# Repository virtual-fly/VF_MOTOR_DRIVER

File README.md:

# VF_Motor_Driver

**VF_Motor_Driver** is an open hardware power distribution board, designed to be part of a larger modular system.  
This design is **based in part** on the [OpenFFBoard TMC4671 driver board](https://github.com/Ultrawipf/OpenFFBoard-hardware), licensed under the GNU General Public License version 3 (GPLv3).

This repository contains the complete schematic and PCB layout for the VF_Motor_Driver board.

---

## 🧩 Project Contents

- KiCad schematic files (`.kicad_sch`)
- KiCad PCB layout files (`.kicad_pcb`)
- `Library/` – Custom library symbols (if any)
- `LICENSE` – Full text of the GNU GPLv3 license
- `README.md` – Project information and license notice

---

## 🔍 Licensing

The hardware design files for **VF_Motor_Driver** are released under the terms of the **GNU General Public License, version 3 (GPLv3)**.

You are free to:
- Use and manufacture this hardware for any purpose
- Study, modify and redistribute the design
- Include this design in your own open projects

**Conditions**:
- You must publish any modified versions under the same GPLv3 license
- You must attribute the original author(s)
- You must make the complete design files available to your users if you distribute products based on this design

Author: Enric Garcia Diaz

Copyright (c) 2025 VirtualFly S.L.

See the `LICENSE` file for full details.

---

## ⚠️ Integration Notice

The VF_Motor_Driver is used as a subsystem in a commercial product developed by VirtualFly S.L.

> The VF_Motor_Driver hardware is GPLv3-licensed,  
> but the **microcontroller board and its firmware** are **not included** in this repository and are **not derived** from any GPLv3-licensed work.

---

## 📘 Attribution Notice

The microcontroller board and its firmware used in the final product are derived from the open-source project [OpenFFBoard](https://github.com/Ultrawipf/OpenFFBoard), originally developed by Yannick Richter and released under the MIT License.

The original license terms and copyright notice are preserved.

This firmware and MCU board are not included in this repository and are not covered by the GPLv3 license.

---

## 🔌 Compatibility

The VF_Motor_Driver is designed to interface with a microcontroller unit (MCU) that is electrically and functionally compatible with the [OpenFFBoard](https://github.com/Ultrawipf/OpenFFBoard) open-source project.

> The OpenFFBoard firmware and hardware are **not included** in this repository  
> and are released under the [MIT License](https://opensource.org/licenses/MIT).

Compatible with OpenFFBoard, but **designed, tested, and supported by VirtualFly** for professional use cases.

This compatibility is provided as a convenience for developers and users who already rely on the OpenFFBoard ecosystem or wish to integrate the VF_Motor_Driver into similar setups.

---

## 🤝 Contribution to the Open Source Community

The VF_Motor_Driver project is part of VirtualFly’s commitment to supporting open hardware and fostering collaboration with the developer community.

By releasing this board under the GNU GPLv3 license, we aim to:

- ✅ Provide a solid and reusable foundation for motor control and power distribution in open systems
- ✅ Extend compatibility with the existing [OpenFFBoard](https://github.com/Ultrawipf/OpenFFBoard) ecosystem
- ✅ Offer a real-world example of how open-source hardware can coexist with commercial products
- ✅ Help engineers, makers, and researchers save time and improve reliability in their own designs

We believe that innovation grows stronger when shared.  
We encourage developers to build upon this work, suggest improvements, and share their own adaptations.

If you use this project, improve it, or integrate it into a new design, feel free to [get in touch](mailto:support@virtual-fly.com) or contribute via pull requests.

Together, we can strengthen the open hardware movement.

---

## 📞 Contact

**VirtualFly S.L.**  
Website: [https://virtual-fly.com](https://virtual-fly.com)  
Email: [support@virtual-fly.com](mailto:support@virtual-fly.com)

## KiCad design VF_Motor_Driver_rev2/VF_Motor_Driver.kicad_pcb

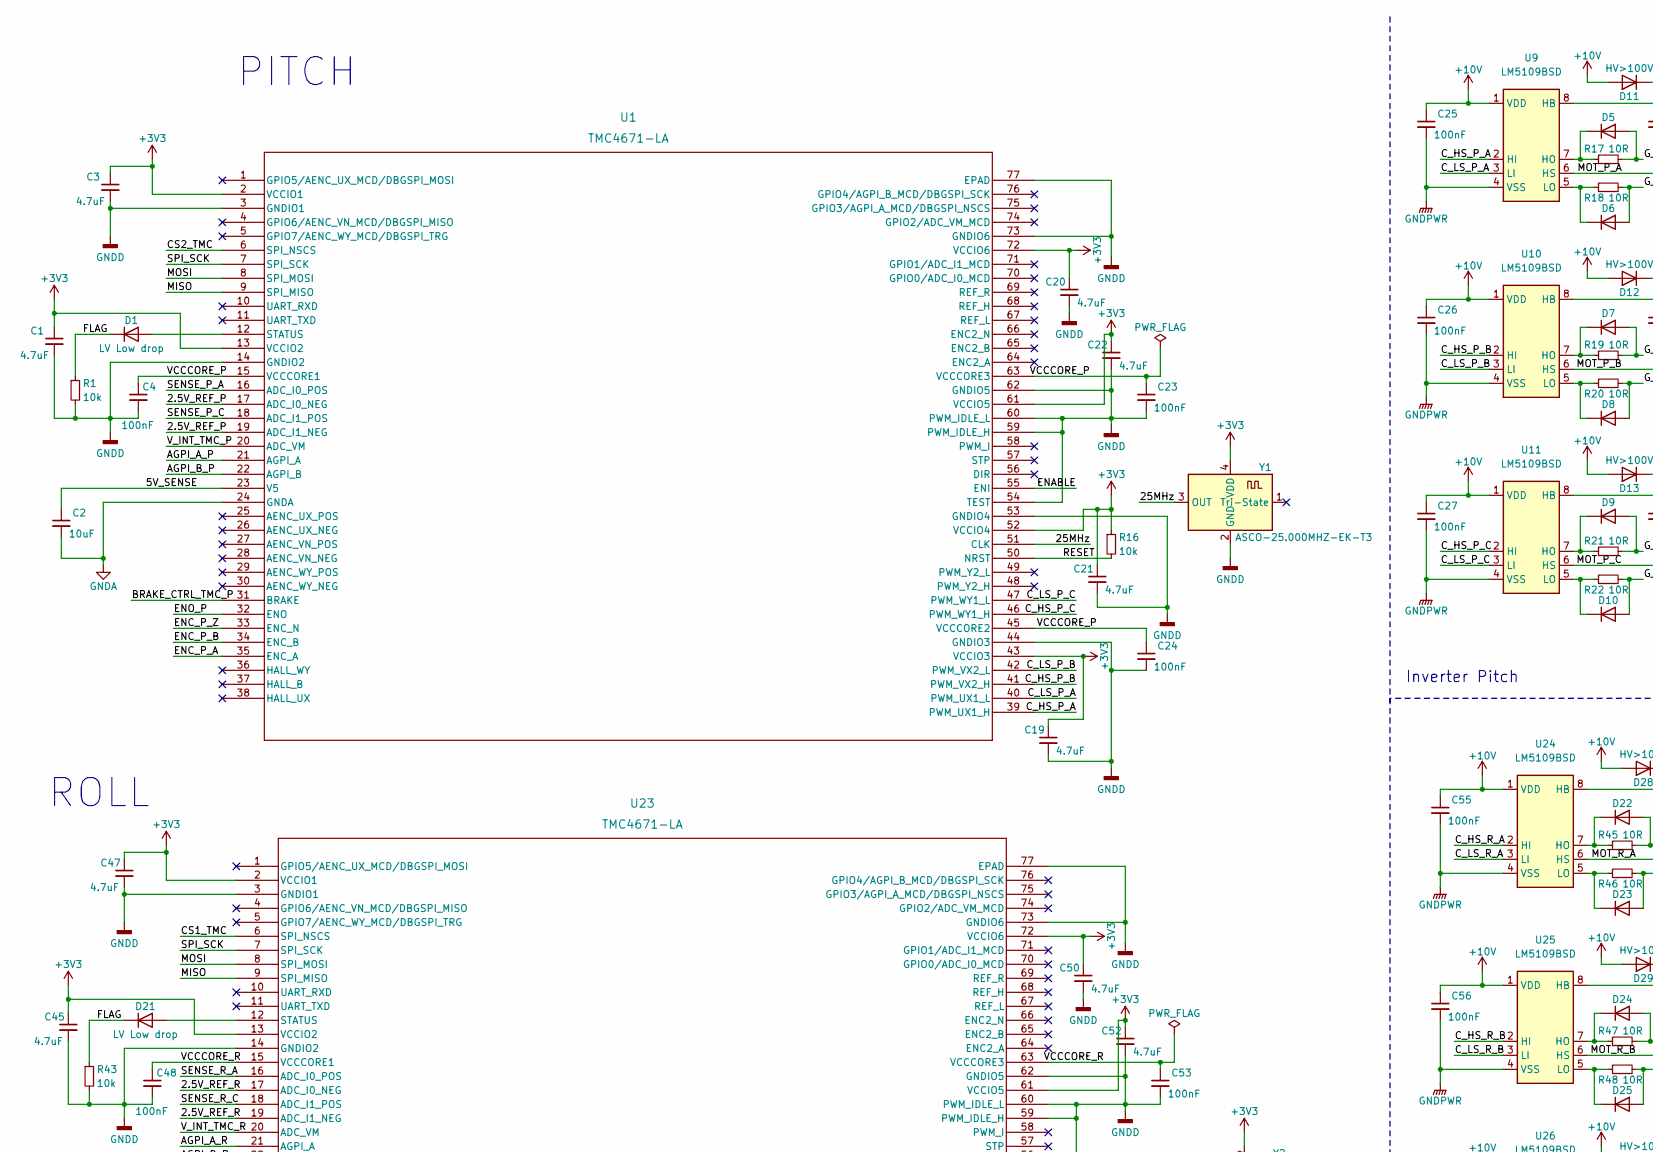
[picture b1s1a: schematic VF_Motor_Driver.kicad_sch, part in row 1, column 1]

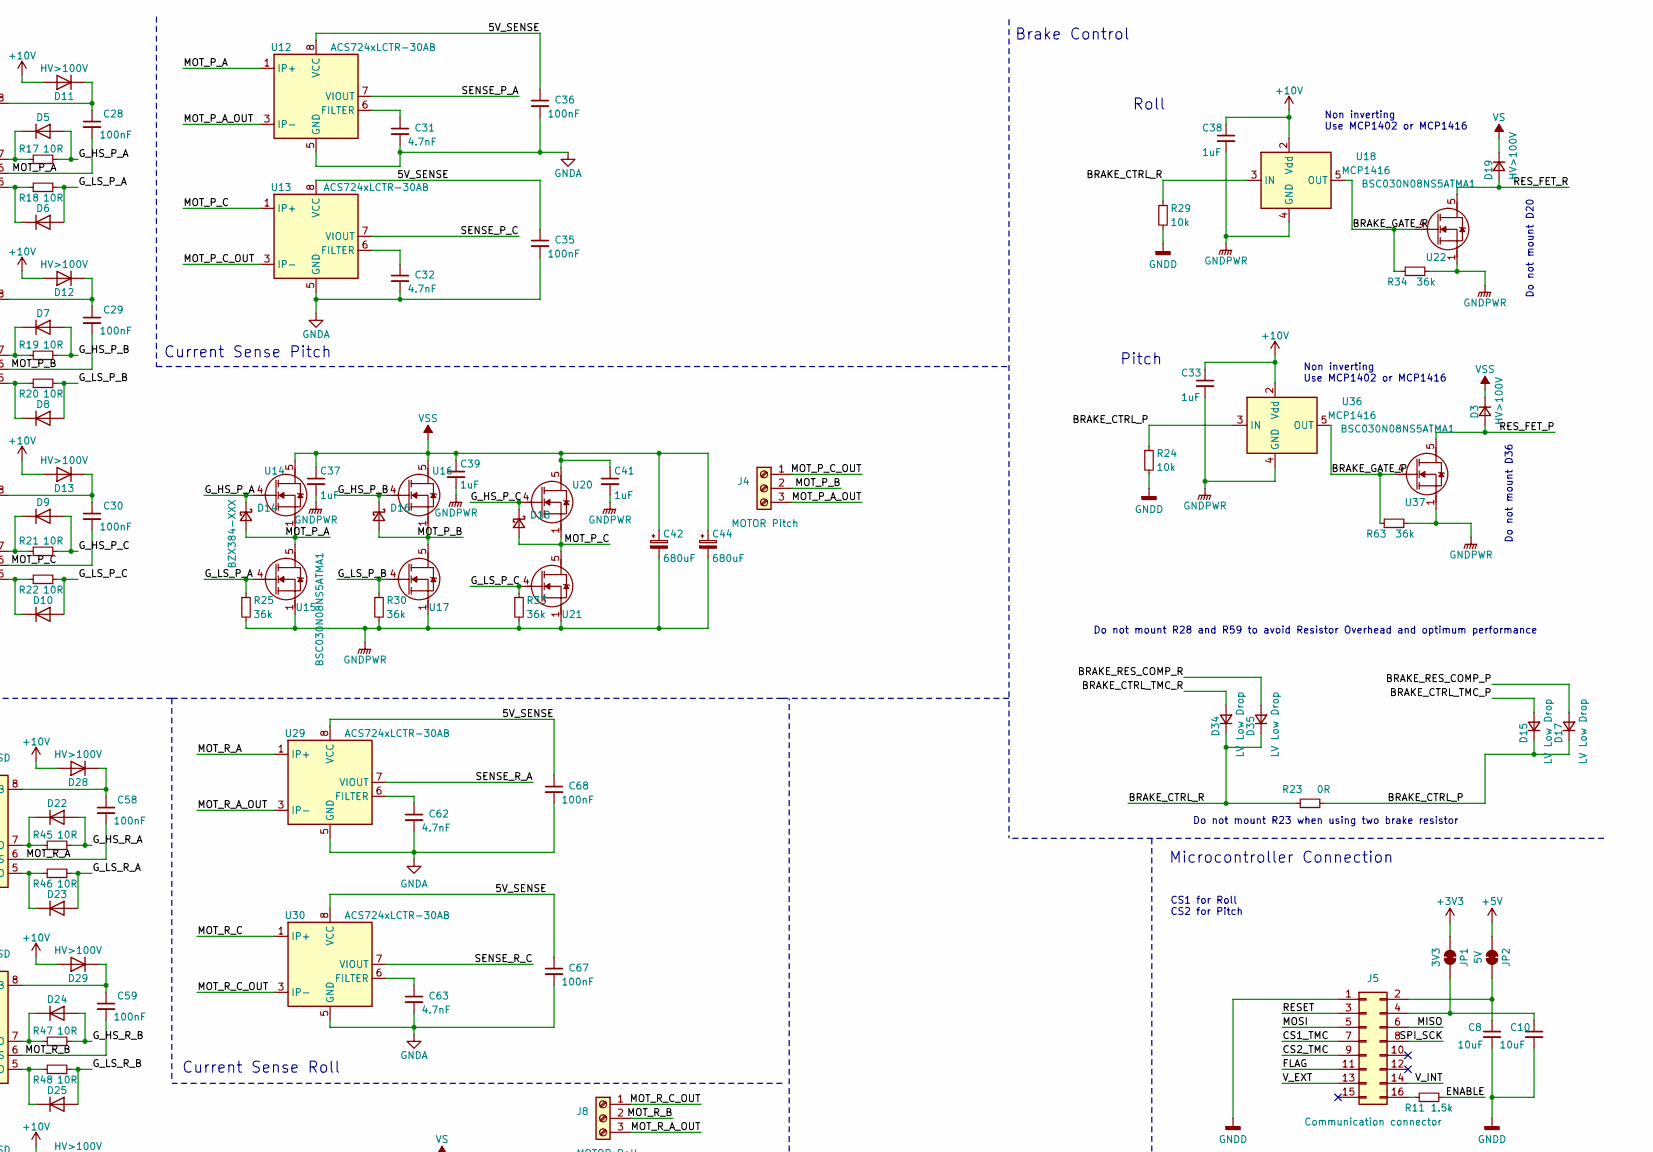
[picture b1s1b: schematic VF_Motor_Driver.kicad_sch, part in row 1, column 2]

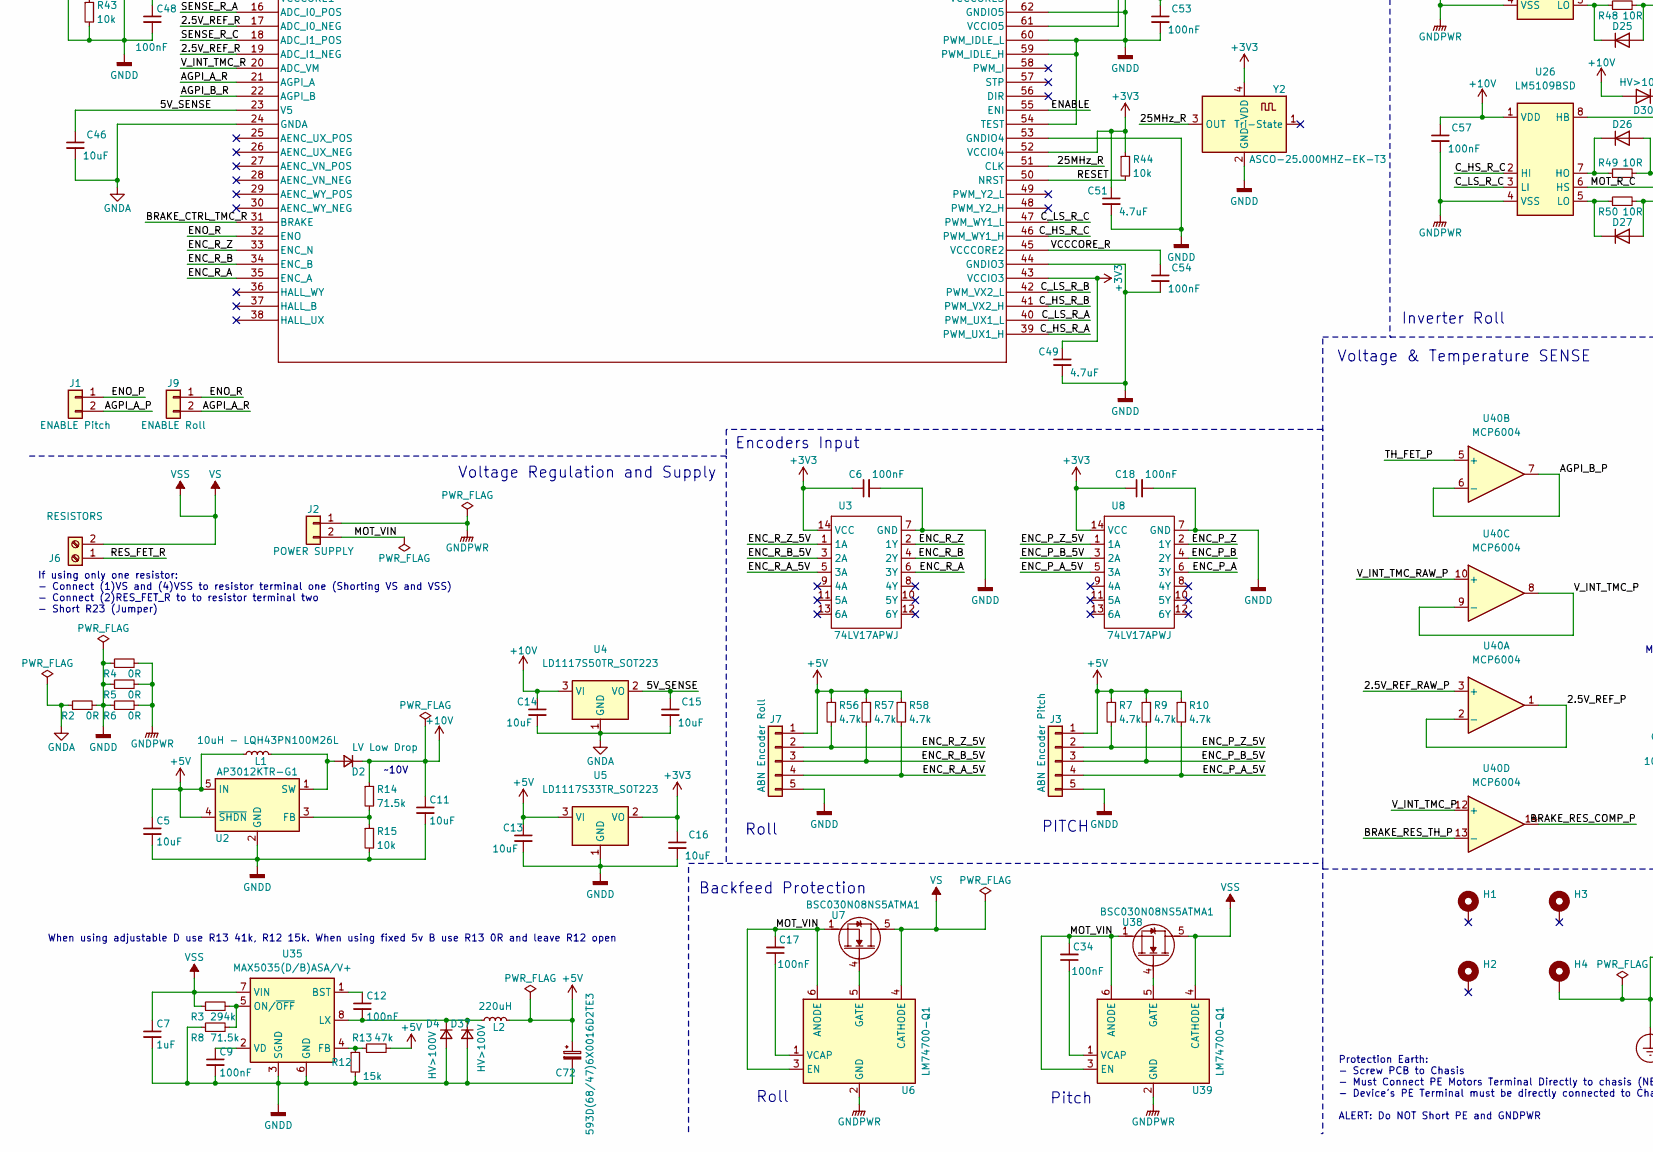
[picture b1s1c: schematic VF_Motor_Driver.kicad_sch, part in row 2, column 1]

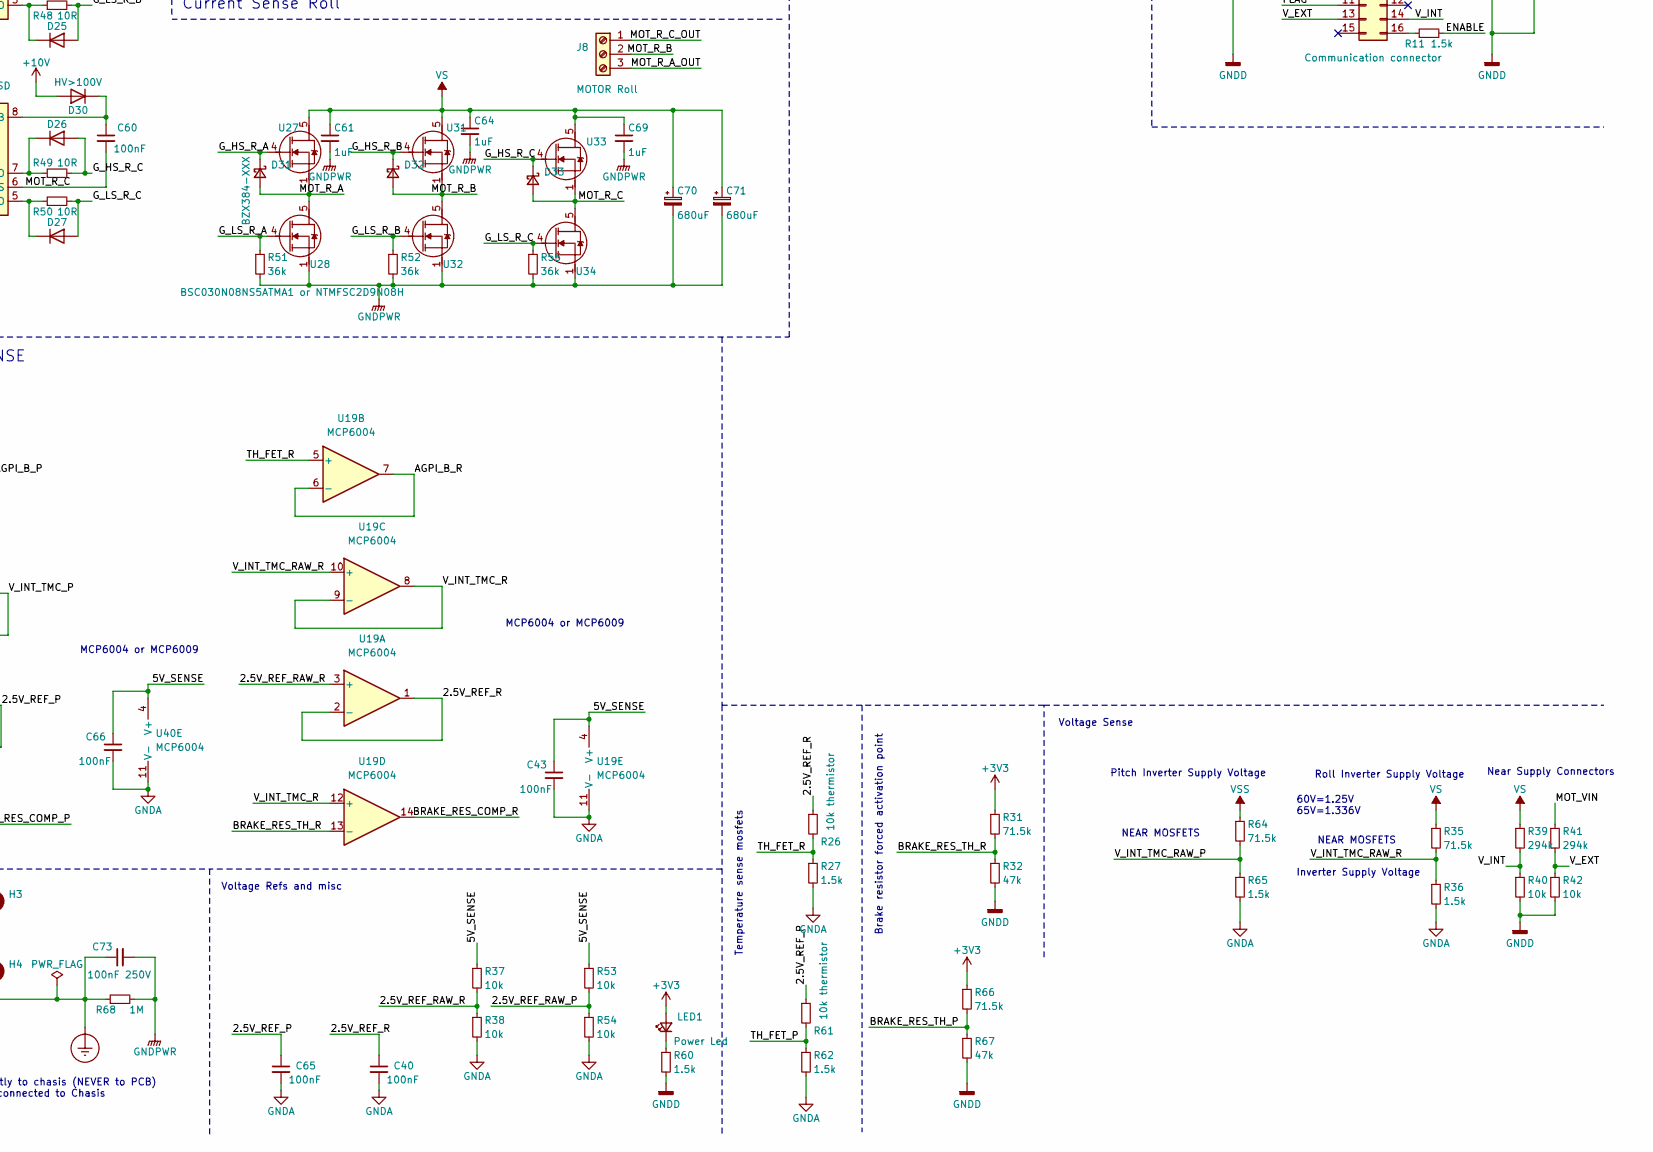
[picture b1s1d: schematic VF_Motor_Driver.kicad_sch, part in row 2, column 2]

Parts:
C1, C3, C19, C20, C21, C22, C45, C47, C49, C50, C51, C52: 4.7uF; C_0603_1608Metric
C2, C5, C8, C10, C11, C13, C14, C15, C16, C46: 10uF; C_0805_2012Metric
C4, C6, C9, C12, C17, C18, C23, C24, C25, C26, C27, C28, C29, C30, C34, C35, C36, C40, C43, C48, C53, C54, C55, C56, C57, C58, C59, C60, C65, C66, C67, C68: 100nF; C_0603_1608Metric
C7, C33, C37, C38, C39, C41, C61, C64, C69: 1uF; C_1206_3216Metric
C31, C32, C62, C63: 4.7nF; C_0603_1608Metric
C42, C44, C70, C71: 680uF; CP_Radial_D16.0mm_P7.50mm
C72: 593D(68/47)6X0016D2TE3; CP_EIA-7343-31_Kemet-D
C73: 100nF 250V; C_Disc_D7.5mm_W5.0mm_P7.50mm; JLCPCB C342770
D1, D21: LV Low drop; D_SOD-123F
D2, D15, D17, D34, D35: LV Low Drop; D_SOD-123F
D3, D4, D11, D12, D13, D19, D28, D29, D30: HV>100V; D_SOD-123F
D5, D6, D7, D8, D9, D10, D22, D23, D24, D25, D26, D27: D; D_SOD-123F
D14, D16, D18, D31, D32, D33: BZX384-XXX; D_SOD-323
D37: HV>100V; D_SMA
H1, H2, H3, H4: MountingHole_Pad; MountingHole_3.2mm_M3_Pad
J1: ENABLE Pitch; PinHeader_1x02_P2.54mm_Vertical
J2: POWER SUPPLY; JST_VH_B2P-VH-B_1x02_P3.96mm_Vertical
J3: ABN Encoder Pitch; JST_PH_B5B-PH-K_1x05_P2.00mm_Vertical; JLCPCB C157993
J4: MOTOR Pitch; JST_VH_B3P-VH-B_1x03_P3.96mm_Vertical; JLCPCB C72334
J5: Communication connector; IDC-Header_2x08_P2.54mm_Vertical
J6: RESISTORS; JST_VH_B2P-VH-B_1x02_P3.96mm_Vertical
J7: ABN Encoder Roll; JST_PH_B5B-PH-K_1x05_P2.00mm_Vertical
J8: MOTOR Roll; JST_VH_B3P-VH-B_1x03_P3.96mm_Vertical; JLCPCB C72334
J9: ENABLE Roll; PinHeader_1x02_P2.54mm_Vertical
JP1: 3V3; R_0805_2012Metric
JP2: 5V; R_0805_2012Metric
L1: 10uH - LQH43PN100M26L; L_1812_4532Metric; JLCPCB C99792
L2: 220uH; L_Wurth_WE-LQS-8065
LED1: Power Led; LED_0805_2012Metric; JLCPCB C2297
R1, R15, R16, R24, R29, R37, R38, R40, R42, R43, R44, R53, R54: 10k; R_0603_1608Metric
R2, R4, R5, R6, R23: 0R; R_0603_1608Metric
R3, R39, R41: 294k; R_0603_1608Metric
R7, R9, R10, R56, R57, R58: 4.7k; R_0603_1608Metric
R8, R14, R31, R35, R64, R66: 71.5k; R_0805_2012Metric
R11, R27, R36, R60, R62, R65: 1.5k; R_0603_1608Metric
R12: 15k; R_0603_1608Metric
R13, R32, R67: 47k; R_0603_1608Metric
R17, R18, R19, R20, R21, R22, R45, R46, R47, R48, R49, R50: 10R; R_0603_1608Metric
R25, R30, R33, R34, R51, R52, R55, R63: 36k; R_0603_1608Metric
R26, R61: 10k thermistor; R_0603_1608Metric
R68: 1M; R_1206_3216Metric; JLCPCB C17927
U1, U23: TMC4671-LA; QFN76_10P5X6P5_TRI
U2: AP3012KTR-G1; SOT-23-5
U3, U8: 74LV17APWJ; TSSOP-14_4.4x5mm_P0.65mm
U4: LD1117S50TR_SOT223; SOT-223-3_TabPin2
U5: LD1117S33TR_SOT223; SOT-223-3_TabPin2
U6, U39: LM74700-Q1; SOT-23-6
U7, U14, U15, U16, U17, U20, U21, U22, U27, U31, U32, U33, U34, U37, U38: BSC030N08NS5ATMA1; Infineon_PG-TDSON-8_6.15x5.15mm
U9, U10, U11, U24, U25, U26: LM5109BSD; WSON-8-1EP_4x4mm_P0.8mm_EP2.6x3mm
U12, U13, U29, U30: ACS724xLCTR-30AB; SOIC-8_3.9x4.9mm_P1.27mm
U18, U36: MCP1416; SOT-23-5
U19, U40: MCP6004; TSSOP-14_4.4x5mm_P0.65mm
U28: BSC030N08NS5ATMA1 or NTMFSC2D9N08H; Infineon_PG-TDSON-8_6.15x5.15mm
U35: MAX5035(D/B)ASA/V+; SOIC-8_3.9x4.9mm_P1.27mm
Y1, Y2: ASCO-25.000MHZ-EK-T3; Oscillator_SMD_Abracon_ASCO-4Pin_1.6x1.2mm

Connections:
+3V3: C1.1, C3.1, C6.1, C16.1, C18.1, C19.1, C20.1, C21.1, C22.1, C45.1, C47.1, C49.1, C50.1, C51.1, C52.1, JP1.2 (B), LED1.2 (A), R16.1, R31.1, R44.1, R66.1, U1.2 (VCCIO1), U1.13 (VCCIO2), U1.43 (VCCIO3), U1.52 (VCCIO4), U1.61 (VCCIO5), U1.72 (VCCIO6), U3.14 (VCC), U5.2 (VO), U8.14 (VCC), U23.2 (VCCIO1), U23.13 (VCCIO2), U23.43 (VCCIO3), U23.52 (VCCIO4), U23.61 (VCCIO5), U23.72 (VCCIO6), Y1.4 (VDD), Y2.4 (VDD)
+5V: C5.1, C13.1, C72.1, J3.1, J7.1, JP2.2 (B), L1.1, L2.2, R7.1, R9.1, R10.1, R13.2, R56.1, R57.1, R58.1, U2.4 (~SHDN), U2.5 (IN), U5.3 (VI)
+10V: C11.1, C14.1, C25.1, C26.1, C27.1, C33.1, C38.1, C55.1, C56.1, C57.1, D2.1 (K), D11.2 (A), D12.2 (A), D13.2 (A), D28.2 (A), D29.2 (A), D30.2 (A), R14.1, U4.3 (VI), U9.1 (VDD), U10.1 (VDD), U11.1 (VDD), U18.2 (Vdd), U24.1 (VDD), U25.1 (VDD), U26.1 (VDD), U36.2 (Vdd)
/2.5V_REF_P: C65.1, R61.1, U1.17 (ADC_I0_NEG), U1.19 (ADC_I1_NEG), U40.1, U40.2 (-)
/2.5V_REF_R: C40.1, R26.1, U19.1, U19.2 (-), U23.17 (ADC_I0_NEG), U23.19 (ADC_I1_NEG)
/2.5V_REF_RAW_P: R53.2, R54.1, U40.3 (+)
/2.5V_REF_RAW_R: R37.2, R38.1, U19.3 (+)
/5V_SENSE: C2.1, C15.1, C35.1, C36.1, C43.1, C46.1, C66.1, C67.1, C68.1, R37.1, R53.1, U1.23 (V5), U4.2 (VO), U12.8 (VCC), U13.8 (VCC), U19.4 (V+), U23.23 (V5), U29.8 (VCC), U30.8 (VCC), U40.4 (V+)
/25MHz: U1.51 (CLK), Y1.3 (OUT)
/25MHz_R: U23.51 (CLK), Y2.3 (OUT)
/AGPI_A_P: J1.2, U1.21 (AGPI_A)
/AGPI_A_R: J9.2, U23.21 (AGPI_A)
/AGPI_B_P: U1.22 (AGPI_B), U40.6 (-), U40.7
/AGPI_B_R: U19.6 (-), U19.7, U23.22 (AGPI_B)
/BRAKE_CTRL_P: D15.1 (K), D17.1 (K), R23.2, R24.1, U36.3 (IN)
/BRAKE_CTRL_R: D34.1 (K), D35.1 (K), R23.1, R29.1, U18.3 (IN)
/BRAKE_CTRL_TMC_P: D15.2 (A), U1.31 (BRAKE)
/BRAKE_CTRL_TMC_R: D34.2 (A), U23.31 (BRAKE)
/BRAKE_GATE_P: R63.1, U36.5 (OUT), U37.4
/BRAKE_GATE_R: R34.1, U18.5 (OUT), U22.4
/BRAKE_RES_COMP_P: D17.2 (A), U40.14
/BRAKE_RES_COMP_R: D35.2 (A), U19.14
/BRAKE_RES_TH_P: R66.2, R67.1, U40.13 (-)
/BRAKE_RES_TH_R: R31.2, R32.1, U19.13 (-)
/CS1_TMC: J5.7, U23.6 (SPI_NSCS)
/CS2_TMC: J5.9, U1.6 (SPI_NSCS)
/C_HS_P_A: U1.39 (PWM_UX1_H), U9.2 (HI)
/C_HS_P_B: U1.41 (PWM_VX2_H), U10.2 (HI)
/C_HS_P_C: U1.46 (PWM_WY1_H), U11.2 (HI)
/C_HS_R_A: U23.39 (PWM_UX1_H), U24.2 (HI)
/C_HS_R_B: U23.41 (PWM_VX2_H), U25.2 (HI)
/C_HS_R_C: U23.46 (PWM_WY1_H), U26.2 (HI)
/C_LS_P_A: U1.40 (PWM_UX1_L), U9.3 (LI)
/C_LS_P_B: U1.42 (PWM_VX2_L), U10.3 (LI)
/C_LS_P_C: U1.47 (PWM_WY1_L), U11.3 (LI)
/C_LS_R_A: U23.40 (PWM_UX1_L), U24.3 (LI)
/C_LS_R_B: U23.42 (PWM_VX2_L), U25.3 (LI)
/C_LS_R_C: U23.47 (PWM_WY1_L), U26.3 (LI)
/ENABLE: R11.2, U1.55 (ENI), U23.55 (ENI)
/ENC_P_A: U1.35 (ENC_A), U8.6 (3Y)
/ENC_P_A_5V: J3.4, R10.2, U8.5 (3A)
/ENC_P_B: U1.34 (ENC_B), U8.4 (2Y)
/ENC_P_B_5V: J3.3, R9.2, U8.3 (2A)
/ENC_P_Z: U1.33 (ENC_N), U8.2 (1Y)
/ENC_P_Z_5V: J3.2, R7.2, U8.1 (1A)
/ENC_R_A: U3.6 (3Y), U23.35 (ENC_A)
/ENC_R_A_5V: J7.4, R58.2, U3.5 (3A)
/ENC_R_B: U3.4 (2Y), U23.34 (ENC_B)
/ENC_R_B_5V: J7.3, R57.2, U3.3 (2A)
/ENC_R_Z: U3.2 (1Y), U23.33 (ENC_N)
/ENC_R_Z_5V: J7.2, R56.2, U3.1 (1A)
/ENO_P: J1.1, U1.32 (ENO)
/ENO_R: J9.1, U23.32 (ENO)
/FLAG: D1.1 (K), D21.1 (K), J5.11, R1.1, R43.1
/G_HS_P_A: D5.2 (A), D14.1 (K), R17.2, U14.4
/G_HS_P_B: D7.2 (A), D16.1 (K), R19.2, U16.4
/G_HS_P_C: D9.2 (A), D18.1 (K), R21.2, U20.4
/G_HS_R_A: D22.2 (A), D31.1 (K), R45.2, U27.4
/G_HS_R_B: D24.2 (A), D32.1 (K), R47.2, U31.4
/G_HS_R_C: D26.2 (A), D33.1 (K), R49.2, U33.4
/G_LS_P_A: D6.2 (A), R18.2, R25.1, U15.4
/G_LS_P_B: D8.2 (A), R20.2, R30.1, U17.4
/G_LS_P_C: D10.2 (A), R22.2, R33.1, U21.4
/G_LS_R_A: D23.2 (A), R46.2, R51.1, U28.4
/G_LS_R_B: D25.2 (A), R48.2, R52.1, U32.4
/G_LS_R_C: D27.2 (A), R50.2, R55.1, U34.4
/MISO: J5.6, U1.9 (SPI_MISO), U23.9 (SPI_MISO)
/MOSI: J5.5, U1.8 (SPI_MOSI), U23.8 (SPI_MOSI)
/MOT_P_A: C28.2, D14.2 (A), U9.6 (HS), U12.1 (IP+), U12.2 (IP+), U14.1, U14.2 (S), U14.3 (S), U15.5
/MOT_P_A_OUT: J4.3, U12.3 (IP-), U12.4 (IP-)
/MOT_P_B: C29.2, D16.2 (A), J4.2, U10.6 (HS), U16.1, U16.2 (S), U16.3 (S), U17.5
/MOT_P_C: C30.2, D18.2 (A), U11.6 (HS), U13.1 (IP+), U13.2 (IP+), U20.1, U20.2 (S), U20.3 (S), U21.5
/MOT_P_C_OUT: J4.1, U13.3 (IP-), U13.4 (IP-)
/MOT_R_A: C58.2, D31.2 (A), U24.6 (HS), U27.1, U27.2 (S), U27.3 (S), U28.5, U29.1 (IP+), U29.2 (IP+)
/MOT_R_A_OUT: J8.3, U29.3 (IP-), U29.4 (IP-)
/MOT_R_B: C59.2, D32.2 (A), J8.2, U25.6 (HS), U31.1, U31.2 (S), U31.3 (S), U32.5
/MOT_R_C: C60.2, D33.2 (A), U26.6 (HS), U30.1 (IP+), U30.2 (IP+), U33.1, U33.2 (S), U33.3 (S), U34.5
/MOT_R_C_OUT: J8.1, U30.3 (IP-), U30.4 (IP-)
/MOT_VIN: C17.2, C34.2, J2.2, R41.1, U6.3 (EN), U6.6 (ANODE), U7.1, U7.2 (S), U7.3 (S), U38.1, U38.2 (S), U38.3 (S), U39.3 (EN), U39.6 (ANODE)
/RESET: J5.3, R16.2, R44.2, U1.50 (NRST), U23.50 (NRST)
/RES_FET_P: D3.2 (A), U37.5
/RES_FET_R: D19.2 (A), J6.1, U22.5
/SENSE_P_A: U1.16 (ADC_I0_POS), U12.7 (VIOUT)
/SENSE_P_C: U1.18 (ADC_I1_POS), U13.7 (VIOUT)
/SENSE_R_A: U23.16 (ADC_I0_POS), U29.7 (VIOUT)
/SENSE_R_C: U23.18 (ADC_I1_POS), U30.7 (VIOUT)
/SPI_SCK: J5.8, U1.7 (SPI_SCK), U23.7 (SPI_SCK)
/TH_FET_P: R61.2, R62.1, U40.5 (+)
/TH_FET_R: R26.2, R27.1, U19.5 (+)
/VCCCORE_P: C4.1, C23.1, C24.1, U1.15 (VCCCORE1), U1.45 (VCCCORE2), U1.63 (VCCCORE3)
/VCCCORE_R: C48.1, C53.1, C54.1, U23.15 (VCCCORE1), U23.45 (VCCCORE2), U23.63 (VCCCORE3)
/V_EXT: J5.13, R41.2, R42.1
/V_INT: J5.14, R39.2, R40.1
/V_INT_TMC_P: U1.20 (ADC_VM), U40.8, U40.9 (-), U40.12 (+)
/V_INT_TMC_R: U19.8, U19.9 (-), U19.12 (+), U23.20 (ADC_VM)
/V_INT_TMC_RAW_P: R64.2, R65.1, U40.10 (+)
/V_INT_TMC_RAW_R: R35.2, R36.1, U19.10 (+)
Earth_Protective: C73.1, H4.1, R68.1
GNDA: C2.2, C14.2, C15.2, C31.2, C32.2, C35.2, C36.2, C40.2, C43.2, C46.2, C62.2, C63.2, C65.2, C66.2, C67.2, C68.2, R2.1, R27.2, R36.2, R38.2, R54.2, R62.2, R65.2, U1.24 (GNDA), U4.1 (GND), U12.5 (GND), U13.5 (GND), U19.11 (V-), U23.24 (GNDA), U29.5 (GND), U30.5 (GND), U40.11 (V-)
GNDD: C1.2, C3.2, C4.2, C5.2, C6.2, C7.2, C8.2, C9.2, C10.2, C11.2, C13.2, C16.2, C18.2, C19.2, C20.2, C21.2, C22.2, C23.2, C24.2, C45.2, C47.2, C48.2, C49.2, C50.2, C51.2, C52.2, C53.2, C54.2, C72.2, D4.2 (A), D37.2 (A), J3.5, J5.1, J7.5, R1.2, R2.2, R4.1, R5.1, R6.1, R8.1, R12.2, R15.2, R24.2, R29.2, R32.2, R40.2, R42.2, R43.2, R60.2, R67.2, U1.3 (GNDIO1), U1.14 (GNDIO2), U1.44 (GNDIO3), U1.53 (GNDIO4), U1.54 (TEST), U1.59 (PWM_IDLE_H), U1.60 (PWM_IDLE_L), U1.62 (GNDIO5), U1.73 (GNDIO6), U1.77 (EPAD), U2.2 (GND), U3.7 (GND), U5.1 (GND), U8.7 (GND), U23.3 (GNDIO1), U23.14 (GNDIO2), U23.44 (GNDIO3), U23.53 (GNDIO4), U23.54 (TEST), U23.59 (PWM_IDLE_H), U23.60 (PWM_IDLE_L), U23.62 (GNDIO5), U23.73 (GNDIO6), U23.77 (EPAD), U35.3 (SGND), U35.6 (GND), Y1.2 (GND), Y2.2 (GND)
GNDPWR: C25.2, C26.2, C27.2, C33.2, C37.2, C38.2, C39.2, C41.2, C42.2, C44.2, C55.2, C56.2, C57.2, C61.2, C64.2, C69.2, C70.2, C71.2, C73.2, J2.1, R4.2, R5.2, R6.2, R25.2, R30.2, R33.2, R34.2, R51.2, R52.2, R55.2, R63.2, R68.2, U6.2 (GND), U9.4 (VSS), U9.9 (VSS), U10.4 (VSS), U10.9 (VSS), U11.4 (VSS), U11.9 (VSS), U15.1, U15.2 (S), U15.3 (S), U17.1, U17.2 (S), U17.3 (S), U18.4 (GND), U21.1, U21.2 (S), U21.3 (S), U22.1, U22.2 (S), U22.3 (S), U24.4 (VSS), U24.9 (VSS), U25.4 (VSS), U25.9 (VSS), U26.4 (VSS), U26.9 (VSS), U28.1, U28.2 (S), U28.3 (S), U32.1, U32.2 (S), U32.3 (S), U34.1, U34.2 (S), U34.3 (S), U36.4 (GND), U37.1, U37.2 (S), U37.3 (S), U39.2 (GND)
unnamed: D1.2 (A), U1.12 (STATUS)
unnamed: D2.2 (A), L1.2, U2.1 (SW)
unnamed: D5.1 (K), R17.1, U9.7 (HO)
unnamed: D6.1 (K), R18.1, U9.5 (LO)
unnamed: D7.1 (K), R19.1, U10.7 (HO)
unnamed: D8.1 (K), R20.1, U10.5 (LO)
unnamed: D9.1 (K), R21.1, U11.7 (HO)
unnamed: D10.1 (K), R22.1, U11.5 (LO)
unnamed: C28.1, D11.1 (K), U9.8 (HB)
unnamed: C29.1, D12.1 (K), U10.8 (HB)
unnamed: C30.1, D13.1 (K), U11.8 (HB)
unnamed: D21.2 (A), U23.12 (STATUS)
unnamed: D22.1 (K), R45.1, U24.7 (HO)
unnamed: D23.1 (K), R46.1, U24.5 (LO)
unnamed: D24.1 (K), R47.1, U25.7 (HO)
unnamed: D25.1 (K), R48.1, U25.5 (LO)
unnamed: D26.1 (K), R49.1, U26.7 (HO)
unnamed: D27.1 (K), R50.1, U26.5 (LO)
unnamed: C58.1, D28.1 (K), U24.8 (HB)
unnamed: C59.1, D29.1 (K), U25.8 (HB)
unnamed: C60.1, D30.1 (K), U26.8 (HB)
unnamed: C12.2, D4.1 (K), D37.1 (K), L2.1, U35.8 (LX)
unnamed: C8.1, J5.2, JP2.1 (A)
unnamed: C10.1, J5.4, JP1.1 (A)
unnamed: J5.16, R11.1
unnamed: LED1.1 (K), R60.1
unnamed: R14.2, R15.1, U2.3 (FB)
unnamed: U6.5 (GATE), U7.4
unnamed: C17.1, U6.1 (VCAP)
unnamed: C31.1, U12.6 (FILTER)
unnamed: C32.1, U13.6 (FILTER)
unnamed: C62.1, U29.6 (FILTER)
unnamed: C63.1, U30.6 (FILTER)
unnamed: C12.1, U35.1 (BST)
unnamed: R12.1, R13.1, U35.4 (FB)
unnamed: R3.2, R8.2, U35.5 (ON/~OFF)
unnamed: C9.1, U35.2 (VD)
unnamed: U38.4, U39.5 (GATE)
unnamed: C34.1, U39.1 (VCAP)
VS: C7.1, C37.1, C39.1, C41.1, C42.1, C44.1, C61.1, C64.1, C69.1, C70.1, C71.1, D3.1 (K), D19.1 (K), J6.2, R3.1, R35.1, R39.1, R64.1, U6.4 (CATHODE), U7.5, U14.5, U16.5, U20.5, U27.5, U31.5, U33.5, U35.7 (VIN), U38.5, U39.4 (CATHODE)

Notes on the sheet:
Do not mount R23 when using two brake resistor
Brake Control
Backfeed Protection
When using adjustable D use R13 41k, R12 15k. When using fixed 5v B use R13 0R and leave R12 open
Temperature sense mosfets
PITCH
ROLL
CS1 for Roll CS2 for Pitch
Voltage Refs and misc
Pitch
Do not mount D20
Voltage Sense
60V=1.25V 65V=1.336V
Do not mount R28 and R59 to avoid Resistor Overhead and optimum performance
Roll
If using only one resistor: - Connect (1)VS and (4)VSS to resistor terminal one (Shorting VS and VSS) - Connect (2)RES_FET_R to to resistor terminal two - Short R23 (Jumper)
Non inverting Use MCP1402 or MCP1416
Current Sense Pitch
NEAR MOSFETS
Roll Inverter Supply Voltage
Pitch Inverter Supply Voltage
Do not mount D36
Protection Earth: - Screw PCB to Chasis - Must Connect PE Motors Terminal Directly to chasis (NEVER to PCB) - Device's PE Terminal must be directly connected to Chasis ALERT: Do NOT Short PE and GNDPWR
Encoders Input
Inverter Pitch
Voltage & Temperature SENSE
MCP6004 or MCP6009
Inverter Roll
Current Sense Roll
Near Supply Connectors
Voltage Regulation and Supply
Microcontroller Connection
Brake resistor forced activation point
~10V
Inverter Supply Voltage

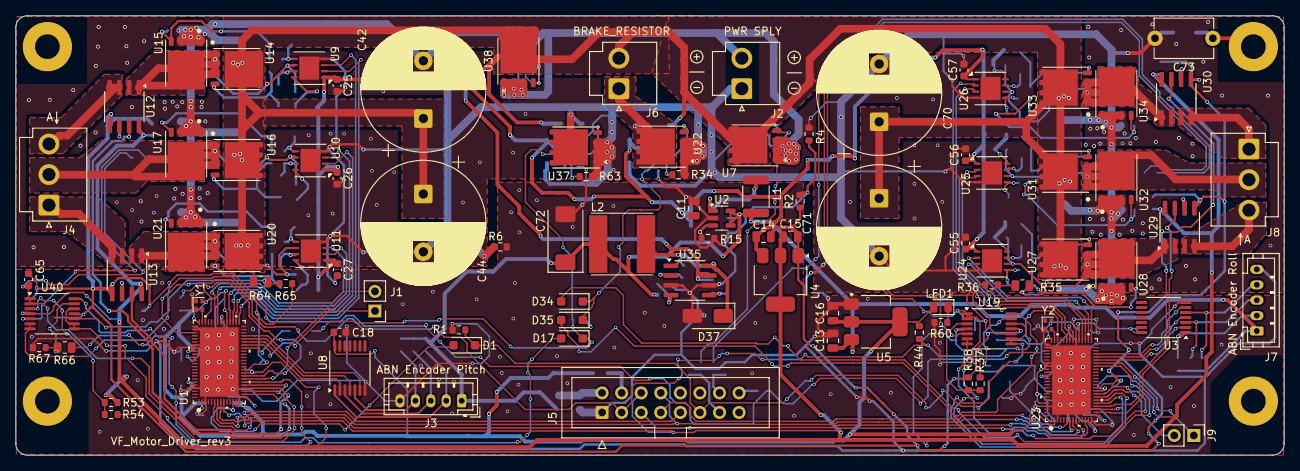
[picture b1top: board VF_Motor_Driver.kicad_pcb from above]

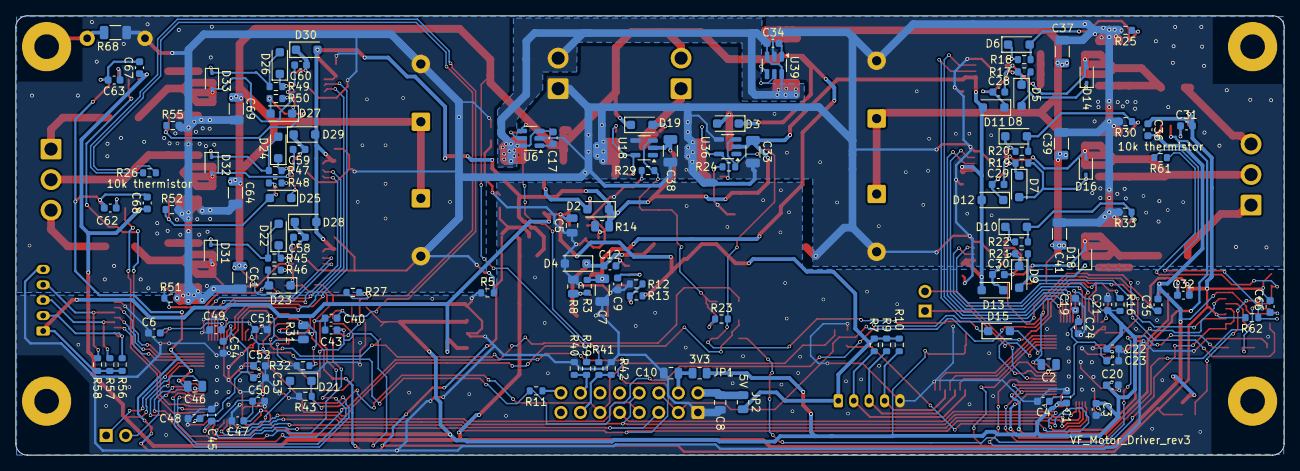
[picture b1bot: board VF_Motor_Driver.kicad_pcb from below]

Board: 2 copper layers, 164.6 x 57.0 mm, 234 parts (137 on the bottom side), 141 nets.

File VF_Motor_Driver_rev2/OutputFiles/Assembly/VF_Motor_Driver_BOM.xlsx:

Comment | Designator | Footprint | LCSC | Comment | Manufacturer | Reference
74LV17APWJ | U8,U3 | TSSOP-14_4.4x5mm_P0.65mm | C7780 |  | Texas Instruments | SN74LV14APWR
100nF | C27,C18,C25,C26,C65,C56,C57,C55,C9,C23,C66,C17,C24,C28,C54,C34,C59,C29,C43,C4,C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 | C_0603_1608Metric | C14663
ABN Encoder Roll | J7 | JST_PH_B5B-PH-K_1x05_P2.00mm_Vertical | C157993
LM5109BSD | U24,U25,U26,U11,U9,U10 | WSON-8-1EP_4x4mm_P0.8mm_EP2.6x3mm | C544701 |  | Texas Instruments | LM5109BSD/NOPB
MCP1416 | U18,U36 | SOT-23-5 | C83775 |  | Microchip Tech | MCP1416T-E/OT
1.5k | R60,R65,R36,R27,R62,R11 | R_0603_1608Metric | C22843
10uF | C14,C13,C11,C15,C16,C46,C5,C2,C8,C10 | C_0805_2012Metric | C440198
HV>100V | D37 | D_SMA | C5241914 |  | VSSAF5M10-M3/H | VSSAF5M10-M3/H
10k | R1,R37,R38,R15,R53,R44,R54,R40,R43,R42,R29,R16,R24 | R_0603_1608Metric | C25804
0R | R4,R6,R2,R5,R23 | R_0603_1608Metric | C21189 | Mount R23 when using only one brake resistor
ABN Encoder Pitch | J3 | JST_PH_B5B-PH-K_1x05_P2.00mm_Vertical | C157993
BSC030N08NS5ATMA1 | U28,U27,U38,U32,U17,U20,U14,U7,U15,U21,U16,U22,U33,U31,U34,U37 | Infineon_PG-TDSON-8_6.15x5.15mm | C3288905 |  | Infineon Technologies | BSC030N08NS5ATMA1
LV Low Drop | D17,D34,D35,D15,D2 | D_SOD-123F | C130413
LD1117S33TR_SOT223 | U5 | SOT-223-3_TabPin2 | C86781
10uH - LQH43PN100M26L | L1 | L_1812_4532Metric | C99792 |  | Murata Electronics | LQH43PN100M26L
POWER SUPPLY / BRAKE RESISTOR | J6,J2 | JST_VH_B2P-VH-B_1x02_P3.96mm_Vertical |  | 10 A with AWG16 wire. Mating: VHR-2N housing + SVH-41T-P1.1 contacts | JST | B2P-VH-B(LF)(SN)
AP3012KTR-G1 | U2 | SOT-23-5 | C102618
LD1117S50TR_SOT223 | U4 | SOT-223-3_TabPin2 | C134077
Power Led | LED1 | LED_0805_2012Metric | C2297
680uF | C71,C42,C70,C44 | CP_Radial_D16.0mm_P7.50mm | C6611961 |  | PANASONIC | EEU-FS1K681B
ACS724xLCTR-30AB | U29,U13,U12,U30 | SOIC-8_3.9x4.9mm_P1.27mm | C141715 |  | Allegro MicroSystems, LLC | ACS724LLCTR-30AB-T
MOTOR Pitch | J4 | JST_VH_B3P-VH-B_1x03_P3.96mm_Vertical |  | 10 A with AWG16 wire. Mating: VHR-3N housing + SVH-41T-P1.1 contacts | JST | B3P-VH-B(LF)(SN)
220uH | L2 | L_Wurth_WE-LQS-8065 | C86663 |  | Sunlord | SWPA8040S221MT
TMC4671-LA | U23,U1 | QFN76_10P5X6P5_TRI | C465954 | Out of Stock | TRINAMIC Motion Control GmbH | TMC4671-LA
ASCO-25.000MHZ-EK-T3 | Y2,Y1 | Oscillator_SMD_Abracon_ASCO-4Pin_1.6x1.2mm | C7503544
593D(68/47)6X0016D2TE3 | C72 | CP_EIA-7343-31_Kemet-D | C1968403 |  | Vishay Intertech | 593D476X9016D2TE3
MOTOR Roll | J8 | JST_VH_B3P-VH-B_1x03_P3.96mm_Vertical |  | 10 A with AWG16 wire. Mating: VHR-3N housing + SVH-41T-P1.1 contacts | JST | B3P-VH-B(LF)(SN)
MAX5035(D/B)ASA/V+ | U35 | SOIC-8_3.9x4.9mm_P1.27mm | C15940 |  | Analog Devices Inc./Maxim Integrated | MAX5035DASA+T
LV Low drop | D1,D21 | D_SOD-123F | C130413
MCP6004 | U40,U19 | TSSOP-14_4.4x5mm_P0.65mm | C50282
Communication connector | J5 | IDC-Header_2x08_P2.54mm_Vertical | C3406
36k | R34,R51,R30,R52,R25,R33,R55,R63 | R_0603_1608Metric | C103579
1uF | C39,C61,C64,C7,C69,C38,C37,C41,C33 | C_1206_3216Metric | C1848
HV>100V | D12,D29,D11,D19,D28,D13,D30,D3 | D_SOD-123F | C64898
HV>100V | D4 | D_SOD-123F | C604266 |  | onsemi | NRVB1H100SFT3G
10R | R17,R19,R48,R22,R20,R49,R50,R46,R47,R21,R45,R18 | R_0603_1608Metric | C22859
47k | R67,R13,R32 | R_0603_1608Metric | C25819
BZX384-XXX | D14,D18,D32,D16,D33,D31 | D_SOD-323 | C295459
10k thermistor | R26,R61 | R_0603_1608Metric | C525381
4.7uF | C52,C3,C1,C45,C49,C20,C47,C51,C21,C22,C19,C50 | C_0603_1608Metric | C19666
4.7k | R9,R7,R58,R10,R56,R57 | R_0603_1608Metric | C23162
294k | R41,R39,R3 | R_0603_1608Metric | C2999562
D | D27,D10,D5,D22,D7,D9,D23,D8,D6,D25,D24,D26 | D_SOD-123F | C64898
71.5k | R64,R35,R66,R31,R8,R14 | R_0805_2012Metric | C2684592
4.7nF | C62,C31,C32,C63 | C_0603_1608Metric | C53987
LM74700-Q1 | U39,U6 | SOT-23-6 | C2941042
5V | JP2 | R_0805_2012Metric | C17477
15k | R12 | R_0603_1608Metric | C22809
3V3 | JP1 | R_0805_2012Metric | C17477
1M | R68 | R_1206_3216Metric | C17927
100nF 250V | C73 | C_Disc_D7.5mm_W5.0mm_P7.50mm | C342770 |  | TDK | CS45-F2GA103M-VKA

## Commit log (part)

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2026-04-09 first commit License GPL v3
2026-04-09 First Commit fork of original project
2026-04-13 Adding Gitignore and correcting contributing file
2026-04-15 updated production characteristics

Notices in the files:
VF_Motor_Driver_rev2/VF_Motor_Driver.kicad_pcb:
Copyright (c) 2025 VirtualFly S.L. Licensed under GNU GPL v3.
